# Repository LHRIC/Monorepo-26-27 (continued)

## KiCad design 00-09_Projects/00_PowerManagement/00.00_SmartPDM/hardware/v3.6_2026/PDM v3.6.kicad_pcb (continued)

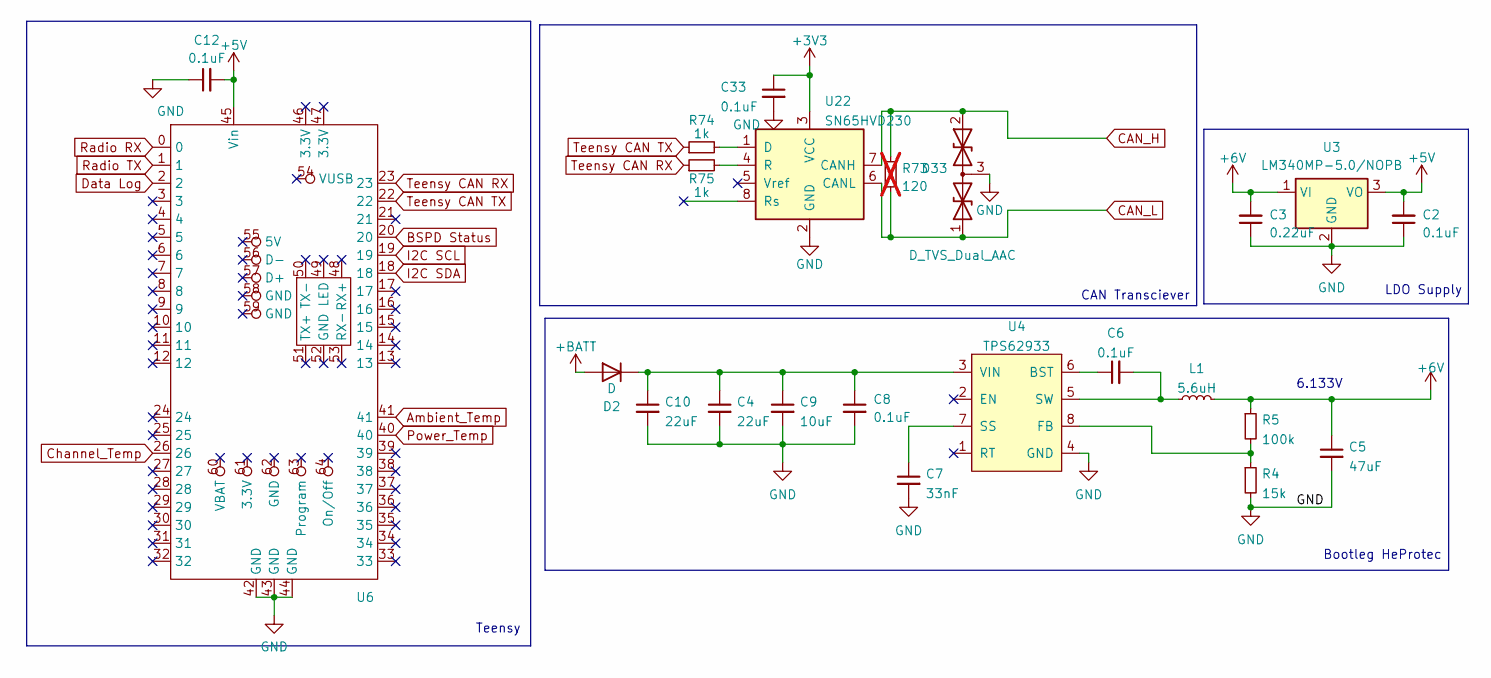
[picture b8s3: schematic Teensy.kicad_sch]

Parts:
C2, C6, C8, C12, C33: 0.1uF; C_0603_1608Metric
C3: 0.22uF; C_0603_1608Metric
C4, C10: 22uF; C_0805_2012Metric
C5: 47uF; C_0603_1608Metric
C7: 33nF; C_0603_1608Metric
C9: 10uF; C_0805_2012Metric
D2: D; D_PowerDI-123
D33: D_TVS_Dual_AAC; SOT-23
L1: 5.6uH; HCMA1305-5R6-R
R4: 15k; R_0603_1608Metric
R5: 100k; R_0603_1608Metric
R73: 120; R_0603_1608Metric; not fitted
R74, R75: 1k; R_0603_1608Metric
U3: LM340MP-5.0/NOPB; SOT-223-3_TabPin2
U4: TPS62933; SOT-583
U6: Teensy 4.1
U22: SN65HVD230; SOIC-8_3.9x4.9mm_P1.27mm

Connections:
+3.3V: C33.1, U22.3 (VCC); also elsewhere on the board
+5V: C2.2, C12.2, U3.3 (VO), U6.45 (Vin)
+6V: C3.2, C5.1, L1.2, R5.1, U3.1 (VI); also elsewhere on the board
+12V: D2.2 (A); also elsewhere on the board
Ambient_Temp: U6.41; also elsewhere on the board
BSPD Status: U6.20; also elsewhere on the board
CAN_H: D33.2 (A2), R73.1, U22.7 (CANH); also elsewhere on the board
CAN_L: D33.1 (A1), R73.2, U22.6 (CANL); also elsewhere on the board
Channel_Temp: U6.26; also elsewhere on the board
Data Log: U6.2; also elsewhere on the board
GND: C2.1, C3.1, C4.2, C5.2, C7.2, C8.2, C9.2, C10.2, C12.1, C33.2, D33.3 (common), R4.2, U3.2 (GND), U4.4 (GND), U6.42 (GND), U6.43 (GND), U6.44 (GND), U22.2 (GND); also elsewhere on the board
I2C SCL: U6.19; also elsewhere on the board
I2C SDA: U6.18; also elsewhere on the board
unnamed: C4.1, C8.1, C9.1, C10.1, D2.1 (K), U4.3 (VIN)
unnamed: C6.1, U4.6 (BST)
unnamed: R4.1, R5.2, U4.8 (FB)
unnamed: C7.1, U4.7 (SS)
unnamed: C6.2, L1.1, U4.5 (SW)
unnamed: R74.2, U22.1 (D)
unnamed: R75.2, U22.4 (R)
Power_Temp: U6.40; also elsewhere on the board
Radio RX: U6.0; also elsewhere on the board
Radio TX: U6.1; also elsewhere on the board
Teensy CAN RX: R75.1, U6.23; also elsewhere on the board
Teensy CAN TX: R74.1, U6.22; also elsewhere on the board

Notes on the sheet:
Teensy
Bootleg HeProtec
LDO Supply
6.133V
CAN Transciever

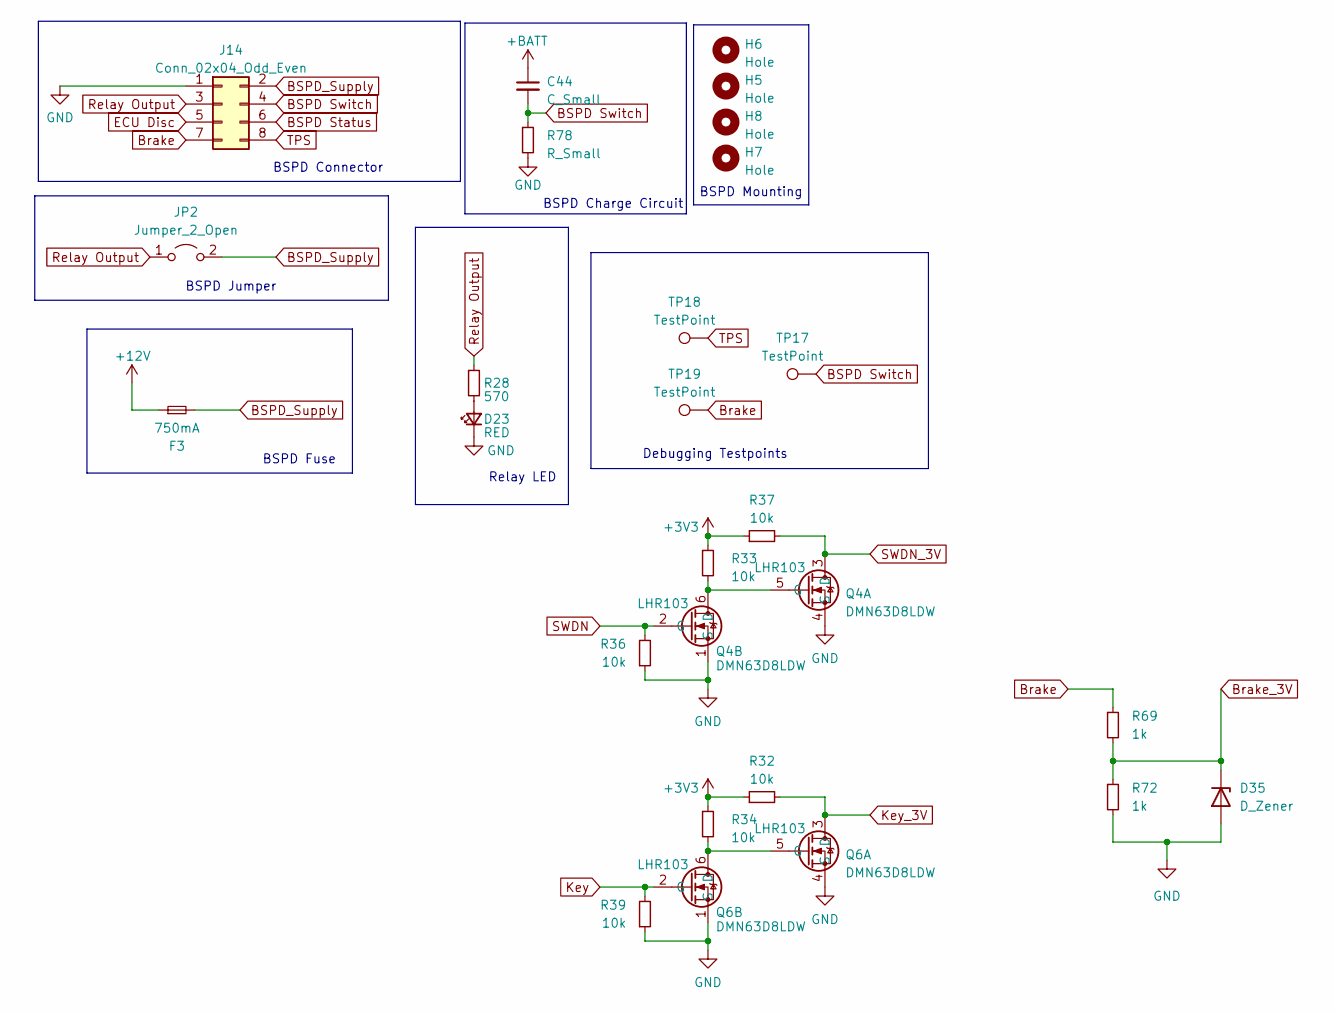
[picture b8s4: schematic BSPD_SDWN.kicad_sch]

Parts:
C44: C_Small; C_0805_2012Metric
D23: RED; LED_0603_1608Metric
D35: D_Zener; D_SOD-123
F3: 750mA; Fuse_1206_3216Metric
H5, H6, H7, H8: Hole; MountingHole_3.7mm
J14: Conn_02x04_Odd_Even; SAMTEC-SFM-104-02-X-D-A
JP2: Jumper_2_Open; SolderJumper-2_P1.3mm_Open_RoundedPad1.0x1.5mm
Q4, Q6: DMN63D8LDW; SOT-363_SC-70-6
R28: 570; R_0603_1608Metric
R32, R33, R34, R36, R37, R39: 10k; R_0603_1608Metric
R69, R72: 1k; R_0603_1608Metric
R78: R_Small; R_0603_1608Metric
TP17, TP18, TP19: TestPoint; TestPoint_Pad_D2.0mm

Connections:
+3.3V: R32.1, R33.1, R34.1, R37.1; also elsewhere on the board
+12V: C44.1, F3.1; also elsewhere on the board
BSPD Status: J14.6; also elsewhere on the board
BSPD Switch: C44.2, J14.4, R78.1, TP17.1
BSPD_Supply: F3.2, J14.2, JP2.2 (B)
Brake: J14.7, R69.1, TP19.1; also elsewhere on the board
Brake_3V: D35.1 (K), R69.2, R72.1; also elsewhere on the board
ECU Disc: J14.5; also elsewhere on the board
GND: D23.1 (K), D35.2 (A), J14.1, Q4.1 (S), Q4.4 (S), Q6.1 (S), Q6.4 (S), R36.1, R39.1, R72.2, R78.2; also elsewhere on the board
Key: Q6.2 (G), R39.2; also elsewhere on the board
Key_3V: Q6.3 (D), R32.2; also elsewhere on the board
unnamed: D23.2 (A), R28.2
unnamed: Q4.5 (G), Q4.6 (D), R33.2
unnamed: Q6.5 (G), Q6.6 (D), R34.2
Relay Output: J14.3, JP2.1 (A), R28.1; also elsewhere on the board
SWDN: Q4.2 (G), R36.2; also elsewhere on the board
SWDN_3V: Q4.3 (D), R37.2; also elsewhere on the board
TPS: J14.8, TP18.1; also elsewhere on the board

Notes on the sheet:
Relay LED
BSPD Mounting
BSPD Fuse
BSPD Connector
BSPD Charge Circuit
BSPD Jumper
Debugging Testpoints

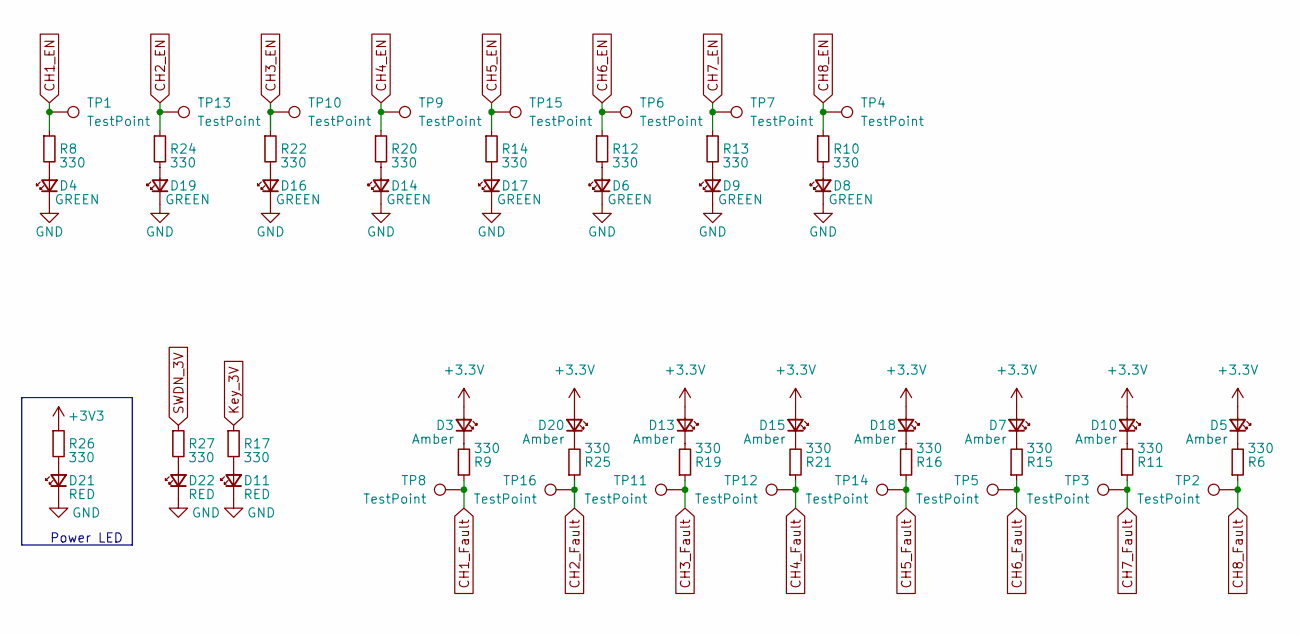
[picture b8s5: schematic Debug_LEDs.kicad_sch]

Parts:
D3, D5, D7, D10, D13, D15, D18, D20: Amber; LED_0603_1608Metric
D4, D6, D8, D9, D14, D16, D17, D19: GREEN; LED_0603_1608Metric
D11, D21, D22: RED; LED_0603_1608Metric
R6, R8, R9, R10, R11, R12, R13, R14, R15, R16, R17, R19, R20, R21, R22, R24, R25, R26, R27: 330; R_0603_1608Metric
TP1, TP2, TP3, TP4, TP5, TP6, TP7, TP8, TP9, TP10, TP11, TP12, TP13, TP14, TP15, TP16: TestPoint; TestPoint_Pad_D1.0mm

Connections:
+3.3V: D3.2 (A), D5.2 (A), D7.2 (A), D10.2 (A), D13.2 (A), D15.2 (A), D18.2 (A), D20.2 (A), R26.1; also elsewhere on the board
CH1_EN: R8.1, TP1.1; also elsewhere on the board
CH1_Fault: R9.1, TP8.1; also elsewhere on the board
CH2_EN: R24.1, TP13.1; also elsewhere on the board
CH2_Fault: R25.1, TP16.1; also elsewhere on the board
CH3_EN: R22.1, TP10.1; also elsewhere on the board
CH3_Fault: R19.1, TP11.1; also elsewhere on the board
CH4_EN: R20.1, TP9.1; also elsewhere on the board
CH4_Fault: R21.1, TP12.1; also elsewhere on the board
CH5_EN: R14.1, TP15.1; also elsewhere on the board
CH5_Fault: R16.1, TP14.1; also elsewhere on the board
CH6_EN: R12.1, TP6.1; also elsewhere on the board
CH6_Fault: R15.1, TP5.1; also elsewhere on the board
CH7_EN: R13.1, TP7.1; also elsewhere on the board
CH7_Fault: R11.1, TP3.1; also elsewhere on the board
CH8_EN: R10.1, TP4.1; also elsewhere on the board
CH8_Fault: R6.1, TP2.1; also elsewhere on the board
GND: D4.1 (K), D6.1 (K), D8.1 (K), D9.1 (K), D11.1 (K), D14.1 (K), D16.1 (K), D17.1 (K), D19.1 (K), D21.1 (K), D22.1 (K); also elsewhere on the board
Key_3V: R17.1; also elsewhere on the board
unnamed: D3.1 (K), R9.2
unnamed: D4.2 (A), R8.2
unnamed: D5.1 (K), R6.2
unnamed: D6.2 (A), R12.2
unnamed: D7.1 (K), R15.2
unnamed: D8.2 (A), R10.2
unnamed: D9.2 (A), R13.2
unnamed: D10.1 (K), R11.2
unnamed: D11.2 (A), R17.2
unnamed: D13.1 (K), R19.2
unnamed: D14.2 (A), R20.2
unnamed: D15.1 (K), R21.2
unnamed: D16.2 (A), R22.2
unnamed: D17.2 (A), R14.2
unnamed: D18.1 (K), R16.2
unnamed: D19.2 (A), R24.2
unnamed: D20.1 (K), R25.2
unnamed: D21.2 (A), R26.2
unnamed: D22.2 (A), R27.2
SWDN_3V: R27.1; also elsewhere on the board

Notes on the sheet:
Power LED

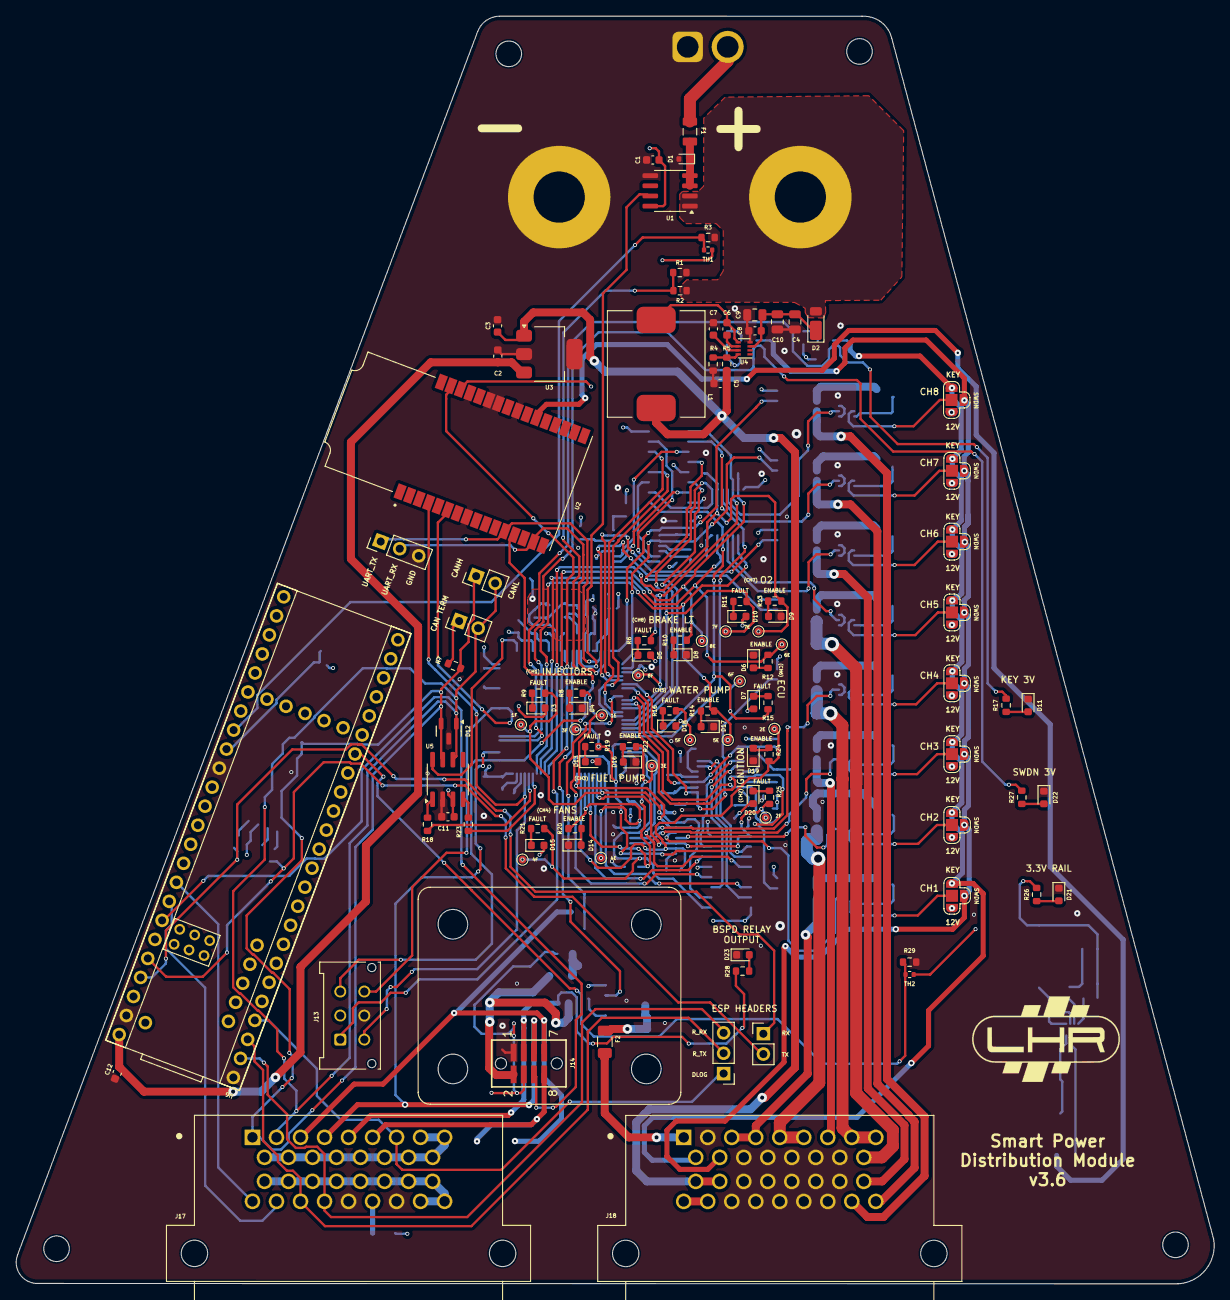
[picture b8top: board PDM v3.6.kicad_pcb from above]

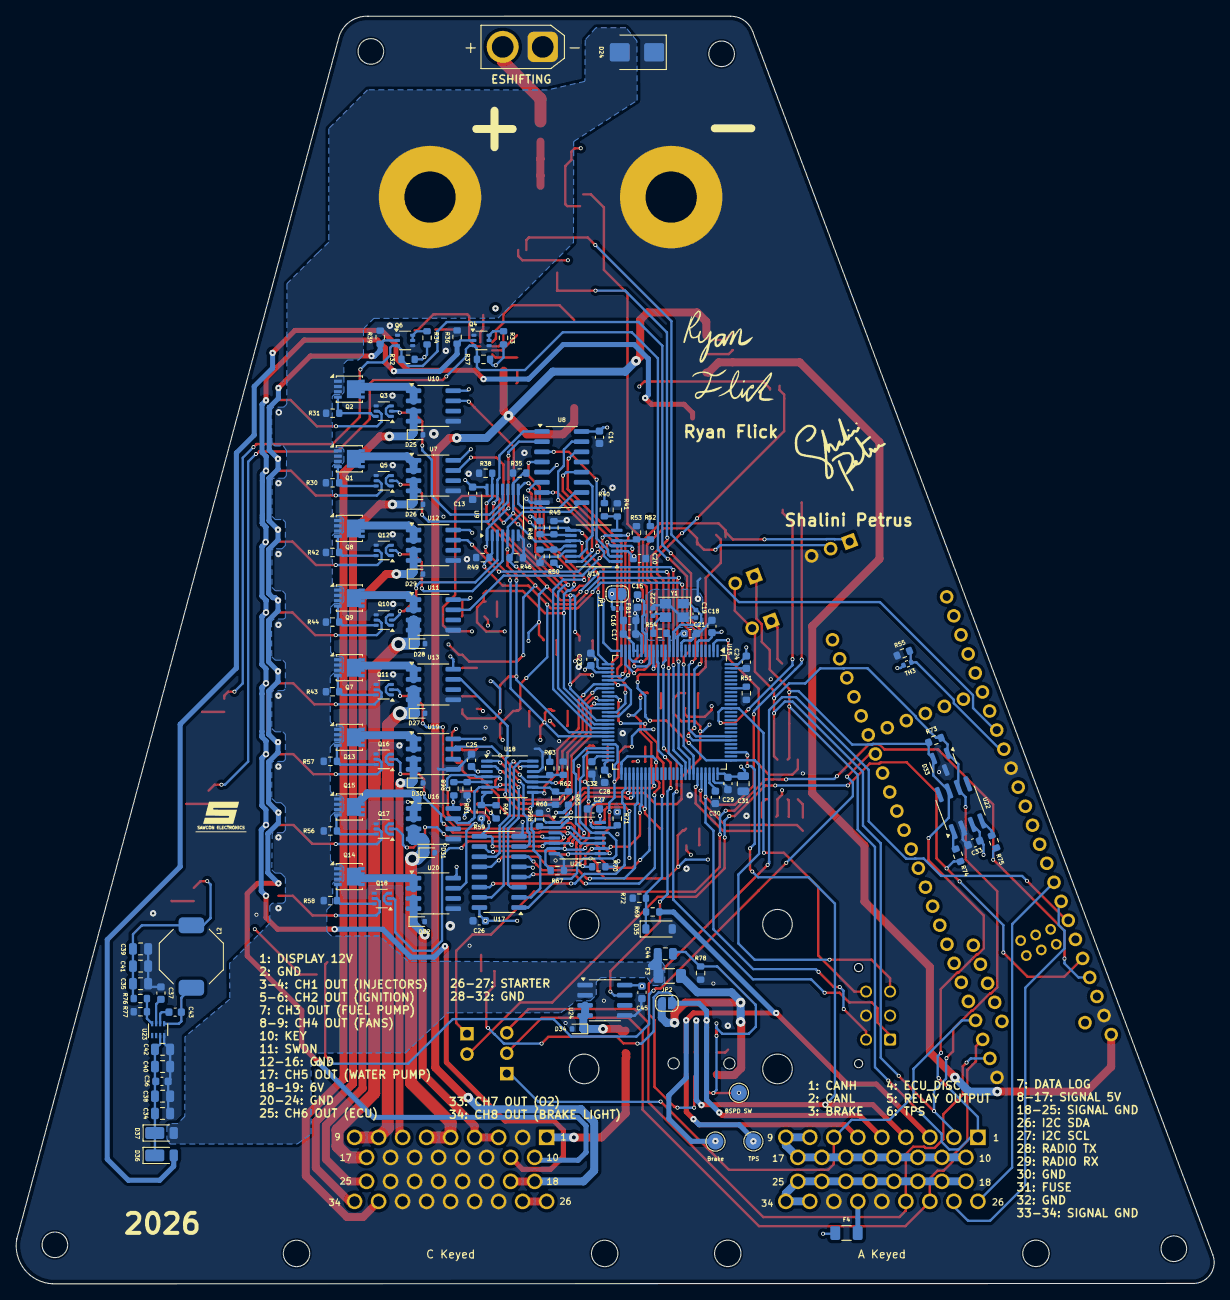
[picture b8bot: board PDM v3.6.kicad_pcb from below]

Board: 4 copper layers, 149.7 x 158.4 mm, 262 parts (143 on the bottom side), 190 nets.

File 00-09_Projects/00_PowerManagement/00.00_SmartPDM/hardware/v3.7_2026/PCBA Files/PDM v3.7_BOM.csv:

Comment,Designator,Footprint,LCSC Part Number
.1uF,"C1, C36, C43, C45",0603,C1591
0.1uF,"C2, C6, C8, C11, C12, C13, C14, C15, C16, C18, C20, C21, C23, C24, C25, C26, C27, C28, C29, C33",0603,C1591
0.22uF,C3,0603,C1591
22uF,"C4, C10, C34, C35, C38, C39, C41",0805,C3909963
47uF,C5,0603,C730416
33nF,"C7, C37",0603,C21117
10uF,"C9, C31",0805,C1713
1uF,C17,0603,C5673
12pF,"C19, C22",0402,C167425
2.2uF,"C30, C32",0603,C71000
4.7uF,"C40, C42",0805,C1779
Schottky Diode,"D1, D25, D26, D27, D28, D29, D30, D31, D32, D34",SOD-523,C3758469
Dual TVS Diode,"D12, D33",SOT-23,C6952426
33.2v TVS Diode,D24,SMB,C88377
Zener Diode,D35,SOD-123,C460914
30A Fuse,F1,,C5467493
750mA,"F2, F3",1206,C2602078
3v3 Fuse,F4,1206,C70071
5.6uH,L1,,C445489
4.7uH,L2,,C1329517
SiS443DN P-MOSFET,"Q1, Q2, Q7, Q8, Q9, Q13, Q14, Q15",,C48586476
MMFTN620KDW-AQ N-MOSFET,"Q3, Q4, Q5, Q6, Q10, Q11, Q12, Q16, Q17, Q18",SOT-363,C6226911
3.9k,R1,0603,C2479414
16k,R2,0603,C2484672
10k,"R3, R29, R30, R31, R32, R33, R34, R35, R36, R37, R38, R39, R42, R43, R44, R46, R49, R51, R55, R56, R57, R58, R66, R67, R70, R71, R77",0603,C2479067
15k,R4,0603,C6112657
100k,R5,0603,C237792
330,"R6, R8, R9, R10, R11, R12, R13, R14, R15, R16, R17, R19, R20, R21, R22, R24, R25, R26, R27",0603,C2479439
1k,"R18, R23, R69, R72, R74, R75",0603,C2484712
570,R28,0603,C2479439
220,R54,0603,C2479616
30.9k,R76,0603,C2479572
Thermistor_NTC,"TH1, TH2, TH3",0402,C3153804
TMCS1108A3UQDR Current Sensor,"U1, U7, U10, U11, U12, U13, U16, U19, U20, U24",SOIC-8,C3684263
LM340MP-5.0/NOPB LDO,U3,SOT-223-3,C131990
TPS62933 ,"U4, U23",SOT-583,C3200405
SN65HVD230,"U5, U22",SOIC-8,C12084
TS3704 Comparator,"U14, U18",TSSOP-14,C75832
STM32F407VET6 Microcontroller,U15,LQFP-100,C28730

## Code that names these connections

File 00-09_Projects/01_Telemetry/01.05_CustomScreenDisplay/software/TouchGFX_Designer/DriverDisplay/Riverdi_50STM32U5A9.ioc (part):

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Mcu.Name=STM32U5A9NJHxQ
Mcu.Package=TFBGA216
Mcu.UserName=STM32U5A9NJHxQ
PA1.Mode=OCTOSPI1_Port1_DQS
PA1.Signal=OCTOSPIM_P1_DQS
PA10.GPIOParameters=GPIO_Speed
PA10.GPIO_Speed=GPIO_SPEED_FREQ_VERY_HIGH
PA10.Mode=OTG/Dual-Role-Device-HS
PA10.Signal=USB_OTG_HS_ID
PA11.GPIOParameters=GPIO_Speed
PA11.GPIO_Speed=GPIO_SPEED_FREQ_VERY_HIGH
PA11.Mode=OTG/Dual-Role-Device-HS
PA11.Signal=USB_OTG_HS_DM
PA12.GPIOParameters=GPIO_Speed
PA12.GPIO_Speed=GPIO_SPEED_FREQ_VERY_HIGH
PA12.Mode=OTG/Dual-Role-Device-HS
PA12.Signal=USB_OTG_HS_DP
PA13\ (JTMS/SWDIO).Mode=Trace_Asynchronous_SW
PA13\ (JTMS/SWDIO).Signal=DEBUG_JTMS-SWDIO
PA14\ (JTCK/SWCLK).Mode=Trace_Asynchronous_SW
PA14\ (JTCK/SWCLK).Signal=DEBUG_JTCK-SWCLK
PA15\ (JTDI).Signal=GPXTI15
PA2.Mode=OCTOSPI1_Port1_NCS
PA2.Signal=OCTOSPIM_P1_NCS
PA3.Signal=ADC2_IN8
PA4.Signal=COMP_DAC11_group
PA5.Signal=COMP_DAC12_group
PA6.Mode=IN11-Differential
PA6.Signal=ADC1_IN11
PA7.Mode=IN11-Differential
PA7.Signal=ADC1_IN12
PA8.Mode=Clock-out
PA8.Signal=RCC_MCO
PA9.Mode=Activate_VBUS_FS
PA9.Signal=USB_OTG_HS_VBUS
PB0.Mode=Output Compare2 CH2N
PB0.Signal=TIM8_CH2N
PB1.Mode=Encoder_mode_occur1
PB1.Signal=LPTIM2_IN1
PB10.Mode=Asynchronous
PB10.Signal=USART3_TX
PB14.Signal=S_TIM15_CH1
PB15.Mode=Encoder_mode_occur1
PB15.Signal=LPTIM2_IN2
PB2.Mode=AlarmB_RoutedAF
PB2.Signal=RTC_OUT2
PB3\ (JTDO/TRACESWO).Mode=Trace_Asynchronous_SW
PB3\ (JTDO/TRACESWO).Signal=DEBUG_JTDO-SWO
PB5.Mode=WakeUp6
PB5.Signal=PWR_WKUP6
PB6.GPIOParameters=GPIO_Speed
PB6.GPIO_Speed=GPIO_SPEED_FREQ_VERY_HIGH
PB6.Mode=I2C
PB6.Signal=I2C4_SCL
PB7.GPIOParameters=GPIO_Speed
PB7.GPIO_Speed=GPIO_SPEED_FREQ_VERY_HIGH
PB7.Mode=I2C
PB7.Signal=I2C4_SDA
PB8.GPIOParameters=GPIO_Speed
PB8.GPIO_Speed=GPIO_SPEED_FREQ_VERY_HIGH
PB8.Mode=FDCAN_Activate
PB8.Signal=FDCAN1_RX
PB9.GPIOParameters=GPIO_Speed
PB9.GPIO_Speed=GPIO_SPEED_FREQ_VERY_HIGH
PB9.Mode=FDCAN_Activate
PB9.Signal=FDCAN1_TX
PC0.Mode=OCTOSPI1_IOH_Port1H
PC0.Signal=OCTOSPIM_P1_IO7
PC1.Mode=OCTOSPI1_IOH_Port1H
PC1.Signal=OCTOSPIM_P1_IO4
PC10.GPIOParameters=GPIO_Speed_High_Only
PC10.GPIO_Speed_High_Only=GPIO_SPEED_FREQ_VERY_HIGH
PC10.Mode=SD_4_bits_Wide_bus
PC10.Signal=SDMMC1_D2
PC11.GPIOParameters=GPIO_Speed_High_Only
PC11.GPIO_Speed_High_Only=GPIO_SPEED_FREQ_VERY_HIGH
PC11.Mode=SD_4_bits_Wide_bus
PC11.Signal=SDMMC1_D3
PC12.GPIOParameters=GPIO_Speed_High_Only
PC12.GPIO_Speed_High_Only=GPIO_SPEED_FREQ_VERY_HIGH
PC12.Mode=SD_4_bits_Wide_bus
PC12.Signal=SDMMC1_CK
PC14-OSC32_IN\ (PC14).Mode=LSE-External-Oscillator
PC14-OSC32_IN\ (PC14).Signal=RCC_OSC32_IN
PC15-OSC32_OUT\ (PC15).Mode=LSE-External-Oscillator
PC15-OSC32_OUT\ (PC15).Signal=RCC_OSC32_OUT
PC2.Mode=OCTOSPI1_IOH_Port1H
PC2.Signal=OCTOSPIM_P1_IO5
PC3.Mode=OCTOSPI1_IOH_Port1H
PC3.Signal=OCTOSPIM_P1_IO6
PC4.GPIOParameters=GPIO_Label
PC4.GPIO_Label=R_INT
PC4.Signal=GPIO_Input
PC5.Mode=Asynchronous
PC5.Signal=USART3_RX
PC6.GPIOParameters=GPIO_Speed
PC6.GPIO_Speed=GPIO_SPEED_FREQ_VERY_HIGH
PC6.Mode=RGB888
PC6.Signal=LTDC_R0
PC7.Signal=S_TIM3_CH2
PC8.GPIOParameters=GPIO_Speed_High_Only
PC8.GPIO_Speed_High_Only=GPIO_SPEED_FREQ_VERY_HIGH
PC8.Mode=SD_4_bits_Wide_bus
PC8.Signal=SDMMC1_D0
PC9.GPIOParameters=GPIO_Speed_High_Only
PC9.GPIO_Speed_High_Only=GPIO_SPEED_FREQ_VERY_HIGH
PC9.Mode=SD_4_bits_Wide_bus
PC9.Signal=SDMMC1_D1
PD0.GPIOParameters=GPIO_Speed
PD0.GPIO_Speed=GPIO_SPEED_FREQ_VERY_HIGH
PD0.Mode=RGB888
PD0.Signal=LTDC_B4
PD1.GPIOParameters=GPIO_Speed
PD1.GPIO_Speed=GPIO_SPEED_FREQ_VERY_HIGH
PD1.Mode=RGB888
PD1.Signal=LTDC_B5
PD10.GPIOParameters=GPIO_Speed
PD10.GPIO_Speed=GPIO_SPEED_FREQ_VERY_HIGH
PD10.Mode=RGB888
PD10.Signal=LTDC_R5
PD11.GPIOParameters=GPIO_Speed
PD11.GPIO_Speed=GPIO_SPEED_FREQ_VERY_HIGH
PD11.Mode=RGB888
PD11.Signal=LTDC_R6
PD12.GPIOParameters=GPIO_Speed
PD12.GPIO_Speed=GPIO_SPEED_FREQ_VERY_HIGH
PD12.Mode=RGB888
PD12.Signal=LTDC_R7
PD13.GPIOParameters=GPIO_Speed
PD13.GPIO_Speed=GPIO_SPEED_FREQ_VERY_HIGH
PD13.Mode=RGB888
PD13.Signal=LTDC_VSYNC
PD14.GPIOParameters=GPIO_Speed
PD14.GPIO_Speed=GPIO_SPEED_FREQ_VERY_HIGH
PD14.Mode=RGB888
PD14.Signal=LTDC_B2
PD15.GPIOParameters=GPIO_Speed
PD15.GPIO_Speed=GPIO_SPEED_FREQ_VERY_HIGH
PD15.Mode=RGB888
PD15.Signal=LTDC_B3
PD2.GPIOParameters=GPIO_Speed_High_Only
PD2.GPIO_Speed_High_Only=GPIO_SPEED_FREQ_VERY_HIGH
PD2.Mode=SD_4_bits_Wide_bus
PD2.Signal=SDMMC1_CMD
PD3.GPIOParameters=GPIO_Speed
PD3.GPIO_Speed=GPIO_SPEED_FREQ_VERY_HIGH
PD3.Mode=RGB888
PD3.Signal=LTDC_CLK
PD8.GPIOParameters=GPIO_Speed
PD8.GPIO_Speed=GPIO_SPEED_FREQ_VERY_HIGH
PD8.Mode=RGB888
PD8.Signal=LTDC_R3
PD9.GPIOParameters=GPIO_Speed
PD9.GPIO_Speed=GPIO_SPEED_FREQ_VERY_HIGH
PD9.Mode=RGB888
PD9.Signal=LTDC_R4
PE0.GPIOParameters=GPIO_Speed
PE0.GPIO_Speed=GPIO_SPEED_FREQ_VERY_HIGH
PE0.Mode=RGB888
PE0.Signal=LTDC_HSYNC
PE1.Mode=Asynchronous
PE1.Signal=USART6_TX
PE10.GPIOParameters=GPIO_Speed
PE10.GPIO_Speed=GPIO_SPEED_FREQ_VERY_HIGH
PE10.Mode=RGB888
PE10.Signal=LTDC_G3
PE11.GPIOParameters=GPIO_Speed
PE11.GPIO_Speed=GPIO_SPEED_FREQ_VERY_HIGH
PE11.Mode=RGB888
PE11.Signal=LTDC_G4
PE12.GPIOParameters=GPIO_Speed
PE12.GPIO_Speed=GPIO_SPEED_FREQ_VERY_HIGH
PE12.Mode=RGB888
PE12.Signal=LTDC_G5
PE13.GPIOParameters=GPIO_Speed
PE13.GPIO_Speed=GPIO_SPEED_FREQ_VERY_HIGH
PE13.Mode=RGB888
PE13.Signal=LTDC_G6
PE14.GPIOParameters=GPIO_Speed
PE14.GPIO_Speed=GPIO_SPEED_FREQ_VERY_HIGH
PE14.Mode=RGB888
PE14.Signal=LTDC_G7
PE15.GPIOParameters=GPIO_Speed
PE15.GPIO_Speed=GPIO_SPEED_FREQ_VERY_HIGH
PE15.Mode=RGB888
PE15.Signal=LTDC_R2
PE3.GPIOParameters=GPIO_PuPd,GPIO_Label
PE3.GPIO_Label=CTP_RST
PE3.GPIO_PuPd=GPIO_PULLDOWN
PE3.Signal=GPIO_Output
PE4.Mode=Hardware Flow Control (RS485)
PE4.Signal=USART6_DE
PE5.GPIOParameters=GPIO_Label
PE5.GPIO_Label=USR_LED_1
PE5.Signal=S_TIM3_CH3
PE6.GPIOParameters=GPIO_PuPd,GPIO_Label,GPIO_ModeDefaultEXTI
PE6.GPIO_Label=CTP_INT
PE6.GPIO_ModeDefaultEXTI=GPIO_MODE_IT_FALLING
PE6.GPIO_PuPd=GPIO_PULLUP
PE6.Signal=GPXTI6
PE7.GPIOParameters=GPIO_Speed
PE7.GPIO_Speed=GPIO_SPEED_FREQ_VERY_HIGH
PE7.Mode=RGB888
PE7.Signal=LTDC_B6
PE8.GPIOParameters=GPIO_Speed
PE8.GPIO_Speed=GPIO_SPEED_FREQ_VERY_HIGH
PE8.Mode=RGB888
PE8.Signal=LTDC_B7
PE9.GPIOParameters=GPIO_Speed
PE9.GPIO_Speed=GPIO_SPEED_FREQ_VERY_HIGH
PE9.Mode=RGB888
PE9.Signal=LTDC_G2
PF10.Mode=O1_P1_CLK
PF10.Signal=OCTOSPIM_P1_CLK
PF11.GPIOParameters=GPIO_Speed
PF11.GPIO_Speed=GPIO_SPEED_FREQ_VERY_HIGH
PF11.Mode=RGB888
PF11.Signal=LTDC_DE
PF12.GPIOParameters=GPIO_Speed
PF12.GPIO_Speed=GPIO_SPEED_FREQ_VERY_HIGH
PF12.Mode=RGB888
PF12.Signal=LTDC_B0
PF13.GPIOParameters=GPIO_Speed
PF13.GPIO_Speed=GPIO_SPEED_FREQ_VERY_HIGH
PF13.Mode=RGB888
PF13.Signal=LTDC_B1
PF14.GPIOParameters=GPIO_Speed
PF14.GPIO_Speed=GPIO_SPEED_FREQ_VERY_HIGH
PF14.Mode=RGB888
PF14.Signal=LTDC_G0
PF15.GPIOParameters=GPIO_Speed
PF15.GPIO_Speed=GPIO_SPEED_FREQ_VERY_HIGH
PF15.Mode=RGB888
PF15.Signal=LTDC_G1
PF4.GPIOParameters=GPIO_PuPd,GPIO_Label
PF4.GPIO_Label=R_RST
PF4.GPIO_PuPd=GPIO_PULLDOWN
PF4.Signal=GPIO_Output
PF6.Mode=OCTOSPI1_IOL_Port1L
PF6.Signal=OCTOSPIM_P1_IO3
PF7.Mode=OCTOSPI1_IOL_Port1L
PF7.Signal=OCTOSPIM_P1_IO2
PF8.Mode=OCTOSPI1_IOL_Port1L
PF8.Signal=OCTOSPIM_P1_IO0
PF9.Mode=OCTOSPI1_IOL_Port1L
PF9.Signal=OCTOSPIM_P1_IO1
PG1.GPIOParameters=GPIO_Label
PG1.GPIO_Label=R_CS
PG1.Signal=GPIO_Output
PG10.Mode=Asynchronous
PG10.Signal=USART1_RX
PG13.GPIOParameters=GPIO_Speed
PG13.GPIO_Speed=GPIO_SPEED_FREQ_VERY_HIGH
PG13.Mode=I2C
PG13.Signal=I2C1_SDA
PG14.GPIOParameters=GPIO_Speed
PG14.GPIO_Speed=GPIO_SPEED_FREQ_VERY_HIGH
PG14.Mode=I2C
PG14.Signal=I2C1_SCL
PG2.GPIOParameters=GPIO_Speed
PG2.GPIO_Speed=GPIO_SPEED_FREQ_VERY_HIGH
PG2.Mode=Full_Duplex_Master
PG2.Signal=SPI1_SCK
PG3.GPIOParameters=GPIO_Speed
PG3.GPIO_Speed=GPIO_SPEED_FREQ_VERY_HIGH
PG3.Mode=Full_Duplex_Master
PG3.Signal=SPI1_MISO
PG4.GPIOParameters=GPIO_Speed
PG4.GPIO_Speed=GPIO_SPEED_FREQ_VERY_HIGH
PG4.Mode=Full_Duplex_Master
PG4.Signal=SPI1_MOSI
PG6.GPIOParameters=GPIO_Speed
PG6.GPIO_Speed=GPIO_SPEED_FREQ_VERY_HIGH
PG6.Mode=RGB888
PG6.Signal=LTDC_R1
PG8.GPIOParameters=GPIO_Label
PG8.GPIO_Label=USB_PWR_EN
PG8.Signal=GPIO_Output
PG9.Mode=Asynchronous
PG9.Signal=USART1_TX
PH0-OSC_IN\ (PH0).Mode=HSE-External-Clock-Source
PH0-OSC_IN\ (PH0).Signal=RCC_OSC_IN
PH11.Signal=GPXTI11
PH3-BOOT0.Signal=GPIO_Input
PH4.GPIOParameters=GPIO_Speed
PH4.GPIO_Speed=GPIO_SPEED_FREQ_VERY_HIGH
PH4.Mode=I2C
PH4.Signal=I2C2_SCL
PH5.GPIOParameters=GPIO_Speed
PH5.GPIO_Speed=GPIO_SPEED_FREQ_VERY_HIGH
PH5.Mode=I2C
PH5.Signal=I2C2_SDA
PH7.GPIOParameters=GPIO_Label
PH7.GPIO_Label=LCD_DISP_RESET
PH7.Signal=GPIO_Output
PI0.Signal=S_TIM5_CH4
PI1.GPIOParameters=GPIO_Speed
PI1.GPIO_Speed=GPIO_SPEED_FREQ_VERY_HIGH
PI1.Mode=Full_Duplex_Master
PI1.Signal=SPI2_SCK
PI2.GPIOParameters=GPIO_Speed
PI2.GPIO_Speed=GPIO_SPEED_FREQ_VERY_HIGH
PI2.Mode=Full_Duplex_Master
PI2.Signal=SPI2_MISO
PI3.GPIOParameters=GPIO_Speed
PI3.GPIO_Speed=GPIO_SPEED_FREQ_VERY_HIGH
PI3.Mode=Full_Duplex_Master
PI3.Signal=SPI2_MOSI
PI4.Mode=Activate-Break-Input
PI4.Signal=TIM8_BKIN
PI5.Signal=S_TIM8_CH1
PI6.Signal=GPIO_Output
PJ0.GPIOParameters=GPIO_Label
PJ0.GPIO_Label=USB_OVERCURRENT
PJ0.Signal=GPIO_Input

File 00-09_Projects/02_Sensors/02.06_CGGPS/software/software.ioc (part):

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Mcu.Name=STM32F302C(6-8)Tx
Mcu.Package=LQFP48
Mcu.UserName=STM32F302C8Tx
PA10.Mode=Asynchronous
PA10.Signal=USART1_RX
PA11.Mode=Device
PA11.Signal=USB_DM
PA12.Mode=Device
PA12.Signal=USB_DP
PA13.Mode=Serial_Wire
PA13.Signal=SYS_JTMS-SWDIO
PA14.Mode=Serial_Wire
PA14.Signal=SYS_JTCK-SWCLK
PA2.Mode=Asynchronous
PA2.Signal=USART2_TX
PA3.Mode=Asynchronous
PA3.Signal=USART2_RX
PA4.Mode=NSS_Signal_Hard_Output
PA4.Signal=SPI3_NSS
PA9.Mode=Asynchronous
PA9.Signal=USART1_TX
PB0.Signal=GPIO_Output
PB1.Signal=GPIO_Output
PB10.Signal=GPIO_Input
PB11.Signal=GPIO_Input
PB12.Mode=NSS_Signal_Hard_Input
PB12.Signal=SPI2_NSS
PB13.Mode=Full_Duplex_Master
PB13.Signal=SPI2_SCK
PB14.Mode=Full_Duplex_Master
PB14.Signal=SPI2_MISO
PB15.Mode=Full_Duplex_Master
PB15.Signal=SPI2_MOSI
PB2.Signal=GPIO_Output
PB3.Mode=Full_Duplex_Master
PB3.Signal=SPI3_SCK
PB4.Mode=Full_Duplex_Master
PB4.Signal=SPI3_MISO
PB5.Mode=Full_Duplex_Master
PB5.Signal=SPI3_MOSI
PB7.Signal=GPIO_Output
PB8.Mode=CAN_Activate
PB8.Signal=CAN_RX
PB9.Mode=CAN_Activate
PB9.Signal=CAN_TX
PF0-OSC_IN.Mode=HSE-External-Oscillator
PF0-OSC_IN.Signal=RCC_OSC_IN
PF1-OSC_OUT.Mode=HSE-External-Oscillator
PF1-OSC_OUT.Signal=RCC_OSC_OUT
RCC.HSEPLLFreq_Value=16000000
RCC.HSE_VALUE=16000000
RCC.SYSCLKFreq_VALUE=16000000
RCC.SYSCLKSourceVirtual=RCC_SYSCLKSOURCE_HSE
board=custom

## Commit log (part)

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2026-06-04 Init
2026-06-06 Documentation Base
2026-06-06 Update CI
2026-06-06 Documentation structure defined and tools added to config.
2026-06-07 Added getting started pages.
2026-06-07 Changed directory names
2026-06-07 Update README to point to docs website.
2026-06-14 Added DBC
2026-06-14 Updated and finalized file structure
2026-06-14 Updated CI to reflect new directory for documentation
2026-06-14 Deployed b877213 with MkDocs version: 1.6.1
2026-06-20 Added Smart PDM one pager
2026-06-29 Made final revisions to Smart PDM one-pager (I'm gonna start assigning so watch out)
2026-06-29 Added Power Management folders
2026-06-29 Made .gitkeeps bc i'm retarded lmao
2026-06-29 More empty folders to prep for port over
2026-06-29 Added subfolders bc I forgot the first time
2026-06-29 Added C Library, needs to be tested
    Modified the gitignore to include python virtual environments. Also
    added a note to the DBC library that will inform the user to re-generate
    the C library if they change it. This will become a python script soon
    to make things easier.
2026-06-29 Tested C Library added Docs
2026-06-30 Added all new subcategories and folders. Ready for port over :)
